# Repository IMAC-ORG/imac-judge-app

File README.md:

# IMAC-Judge-App

# For AeroJudge setup instruction please take a look here
## https://github.com/IMAC-ORG/imac-judge-app/tree/main/scripts

# For developer environment please look below

## Requirements
1. VSCode
2. Docker Desktop
3. Score =>v4.70 with services enabled and started
4. Java 17 or later (Java 21 works fine)

## RUN imac-judge-app
1. Open in a dev container
2. Open new terminal
3. Edit the /var/opt/judge/settings.json file with correct host_ip and port that Score is running on. The file is mounted from the .devcontainer/judge folder and can be modified there instead.
```
sudo vi /var/opt/judge/settings.json

eg.
{
  "judge_id":1,
  "line_number":1,
  "score_host":"192.168.8.100",
  "score_http_port":80,
  "language":"en"
}
```
4. Running the app in the dev container
``` 
cd /workspace
mvn spring-boot:run
```
5. Connecting to the dev container can be done in your local browser http://locahost:8080

## Build imac-judge
1. To build the jar file to be deployed to the PI-SCORE unit.
```
cd judge/
./mvnw clean package
```
Binary {build}.jar located in judge/target folder needs to be copied to the device and extracted in /var/opt/judge/bin
Also {build}-figures.zip file needs to be copied to the device and extracted in /var/opt/judge

## RUN imac-judge-app as a docker container (very similar to running in device)
1. Build imac-judge using above instructions
2. Right-click Dockerfile in root folder and choose Build Image... and name tag imacjudgeapp:latest
3. In terminal run: docker run -p 8080:8080 imacjudgeapp:latest
4. Connecting to the image can be done in your local browser http://locahost:8080

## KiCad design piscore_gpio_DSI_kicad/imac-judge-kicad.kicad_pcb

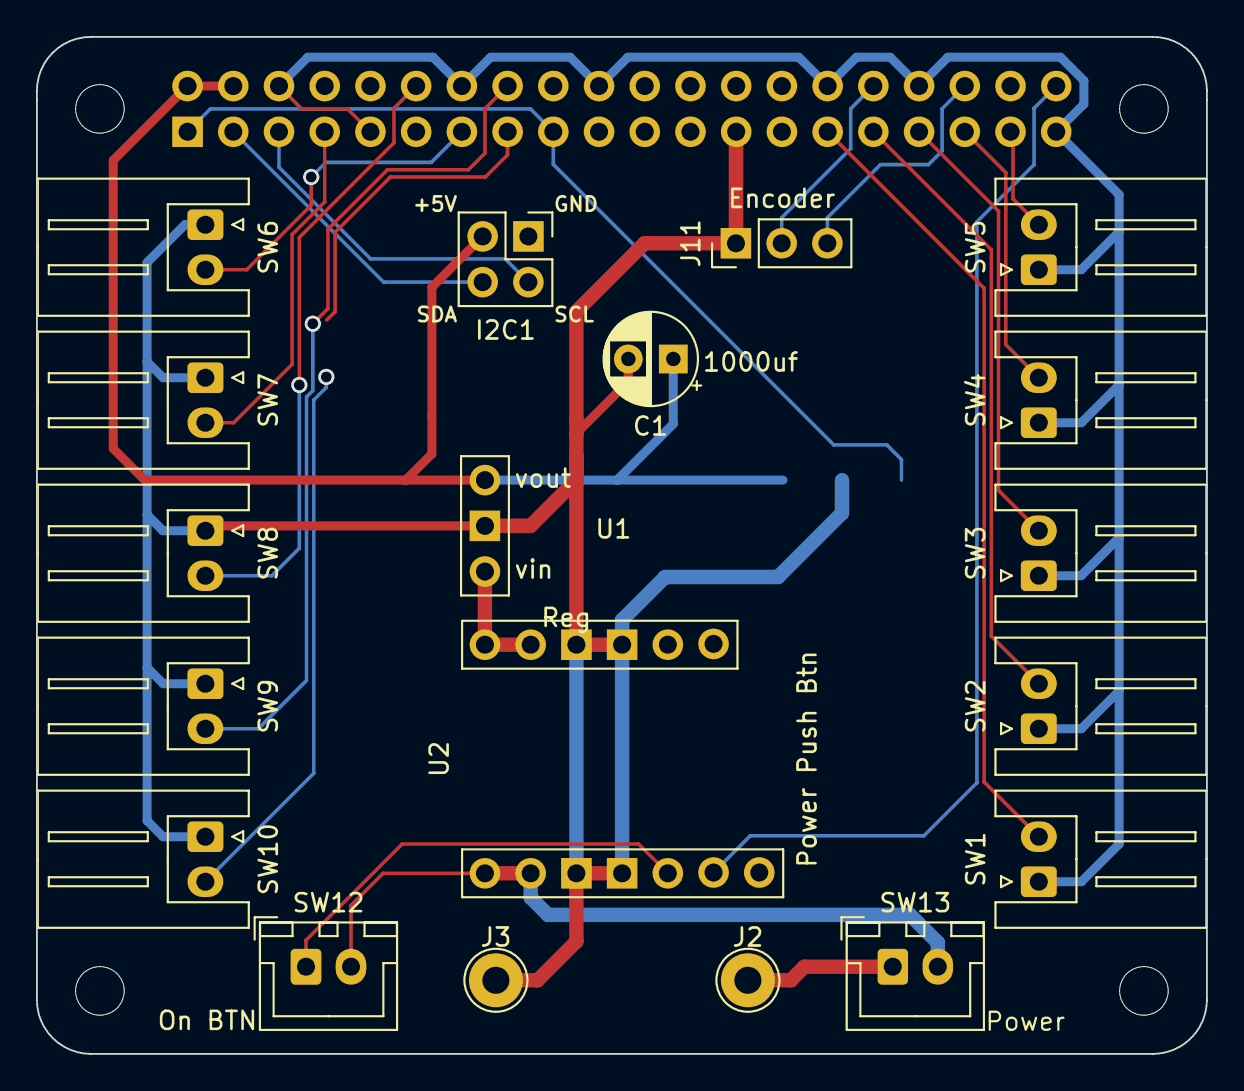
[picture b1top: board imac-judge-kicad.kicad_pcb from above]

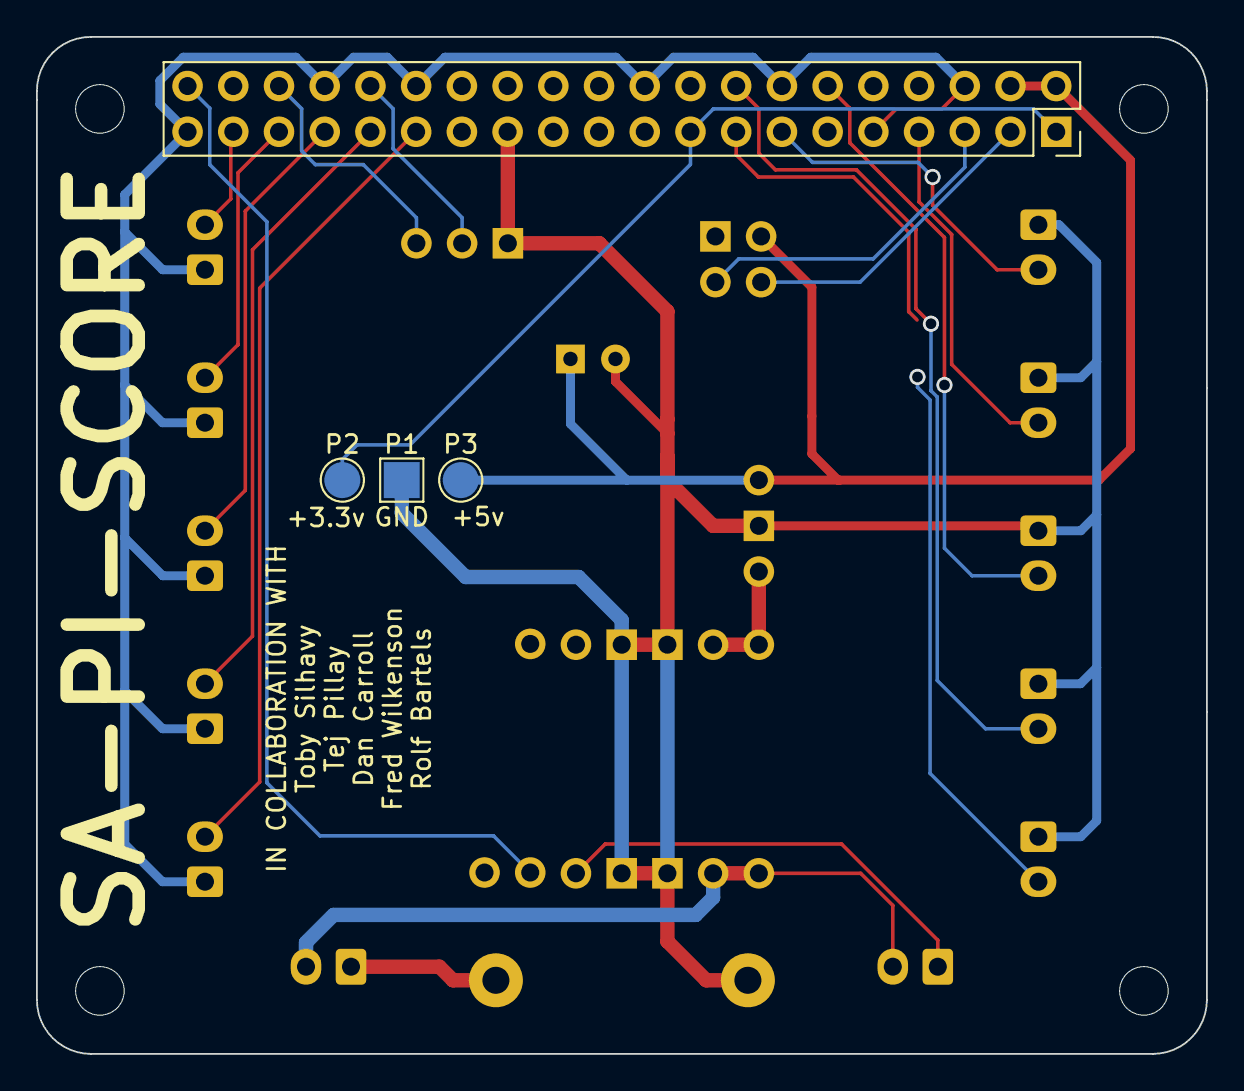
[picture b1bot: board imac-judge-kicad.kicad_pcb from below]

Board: 2 copper layers, 65.0 x 56.5 mm, 27 parts (4 on the bottom side), 22 nets.

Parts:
C1: 1000uf; CP_Radial_D5.0mm_P2.50mm
J1: GPIO; PinSocket_2x20_P2.54mm_Vertical
J2: BATT+; TestPoint_THTPad_D3.0mm_Drill1.5mm
J3: BATT-; TestPoint_THTPad_D3.0mm_Drill1.5mm
J11: Encoder; PinHeader_1x03_P2.54mm_Vertical
MH1, MH2, MH3, MH4: MountingHole_2.7mm_M2.5
P1: GND; TestPoint_Pad_2.0x2.0mm
P2: +3.3v; TestPoint_Pad_D2.0mm
P3: +5v; TestPoint_Pad_D2.0mm
SW1: Button 1; JST_XH_S2B-XH-A_1x02_P2.50mm_Horizontal
SW2: Button 2; JST_XH_S2B-XH-A_1x02_P2.50mm_Horizontal
SW3: Button 3; JST_XH_S2B-XH-A_1x02_P2.50mm_Horizontal
SW4: Button 4; JST_XH_S2B-XH-A_1x02_P2.50mm_Horizontal
SW5: Button 5; JST_XH_S2B-XH-A_1x02_P2.50mm_Horizontal
SW6: Button 6; JST_XH_S2B-XH-A_1x02_P2.50mm_Horizontal
SW7: Button 7; JST_XH_S2B-XH-A_1x02_P2.50mm_Horizontal
SW8: Button 8; JST_XH_S2B-XH-A_1x02_P2.50mm_Horizontal
SW9: Button 9; JST_XH_S2B-XH-A_1x02_P2.50mm_Horizontal
SW10: Button 10; JST_XH_S2B-XH-A_1x02_P2.50mm_Horizontal
SW12: On BTN; JST_XH_B2B-XH-A_1x02_P2.50mm_Vertical
SW13: Power; JST_XH_B2B-XH-A_1x02_P2.50mm_Vertical
U1: Reg; S13V20F5
U2: Power Push Btn; Mini Pushbutton Power Switch
U3: I2C1; PinHeader_2x02_P2.54mm_Vertical

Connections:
+3V3: J1.1, J1.17, P2.1
+5V: C1.1, J1.2, J1.4, P3.1, U1.3 (VOUT), U3.3
+BATT: J2.1, SW13.1 (A)
GND: C1.2, J1.6, J1.9, J1.14, J1.20, J1.25, J1.30, J1.34, J1.39, J3.1, J11.1, P1.1, SW1.1, SW2.1, SW3.1, SW4.1, SW5.1, SW6.1, SW7.1, SW8.1, SW9.1, SW10.1, U1.2 (GND), U2.3 (GND), U2.4 (GND), U3.1
I2C1_SCL: J1.5, U3.2
I2C1_SDA: J1.3, U3.4
Input ENC_A: J1.32, J11.2
Input ENC_B: J1.36, J11.3
Input SW_1: J1.29, SW1.2
Input SW_2: J1.31, SW2.2
Input SW_3: J1.33, SW3.2
Input SW_4: J1.35, SW4.2
Input SW_5: J1.37, SW5.2
Input SW_6: J1.13, SW6.2
Input SW_7: J1.7, SW7.2
Input SW_8: J1.12, SW8.2
Input SW_9: J1.16, SW9.2
Input SW_10: J1.15, SW10.2
MSW: SW12.2, SW13.2 (B), U2.1 (VIN)
PS_BATT+: U1.1 (VIN), U2.2 (VOUT)
PS_OFF: J1.40, U2.7 (OFF)
PS_ON: SW12.1, U2.5 (ON)

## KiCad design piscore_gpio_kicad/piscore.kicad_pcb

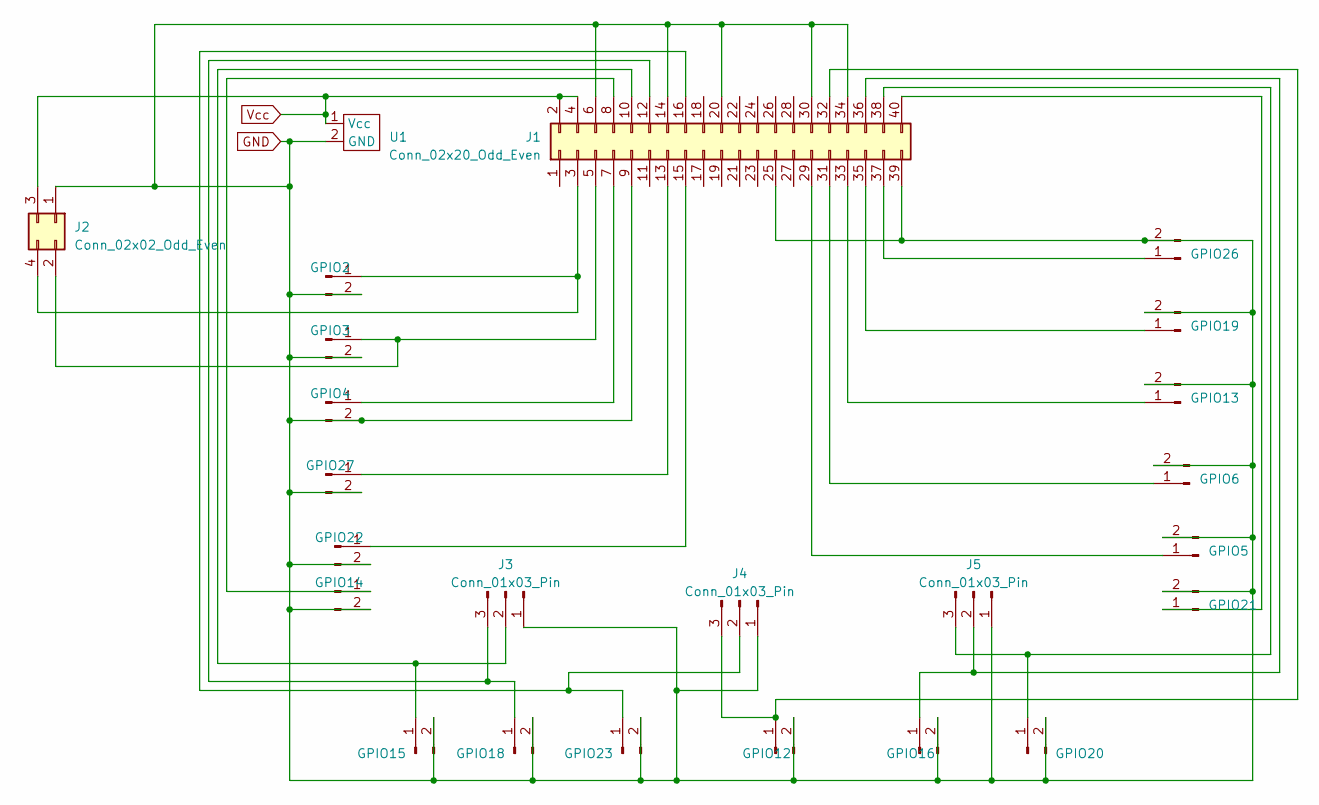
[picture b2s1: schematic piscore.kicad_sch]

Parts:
GPIO2, GPIO3, GPIO4, GPIO5, GPIO6, GPIO12, GPIO13, GPIO14, GPIO15, GPIO16, GPIO18, GPIO19, GPIO20, GPIO21, GPIO22, GPIO23, GPIO26, GPIO27: Conn_01x02_Pin; JST_PH_S2B-PH-K_1x02_P2.00mm_Horizontal
J1: Conn_02x20_Odd_Even; PinHeader_2x20_P2.54mm_Vertical
J2: Conn_02x02_Odd_Even; PinHeader_2x02_P2.54mm_Vertical
J3, J4, J5: Conn_01x03_Pin; PinHeader_1x03_P2.54mm_Vertical
U1: Solder_Pads

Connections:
GND: GPIO2.2, GPIO3.2, GPIO4.2, GPIO5.2, GPIO6.2, GPIO12.2, GPIO13.2, GPIO14.2, GPIO15.2, GPIO16.2, GPIO18.2, GPIO19.2, GPIO20.2, GPIO21.2, GPIO22.2, GPIO23.2, GPIO26.2, GPIO27.2, J1.6, J1.9, J1.14, J1.20, J1.25, J1.30, J1.34, J1.39, J2.1, J3.1, J4.1, J5.1, U1.2 (GND)
unnamed: GPIO2.1, J1.3, J2.4
unnamed: GPIO3.1, J1.5, J2.2
unnamed: GPIO4.1, J1.7
unnamed: GPIO5.1, J1.29
unnamed: GPIO6.1, J1.31
unnamed: GPIO12.1, J1.32, J4.3
unnamed: GPIO13.1, J1.33
unnamed: GPIO14.1, J1.8
unnamed: GPIO15.1, J1.10, J3.2
unnamed: GPIO16.1, J1.36, J5.2
unnamed: GPIO18.1, J1.12, J3.3
unnamed: GPIO19.1, J1.35
unnamed: GPIO20.1, J1.38, J5.3
unnamed: GPIO21.1, J1.40
unnamed: GPIO22.1, J1.15
unnamed: GPIO23.1, J1.16, J4.2
unnamed: GPIO26.1, J1.37
unnamed: GPIO27.1, J1.13
Vcc: J1.2, J1.4, J2.3, U1.1 (Vcc)

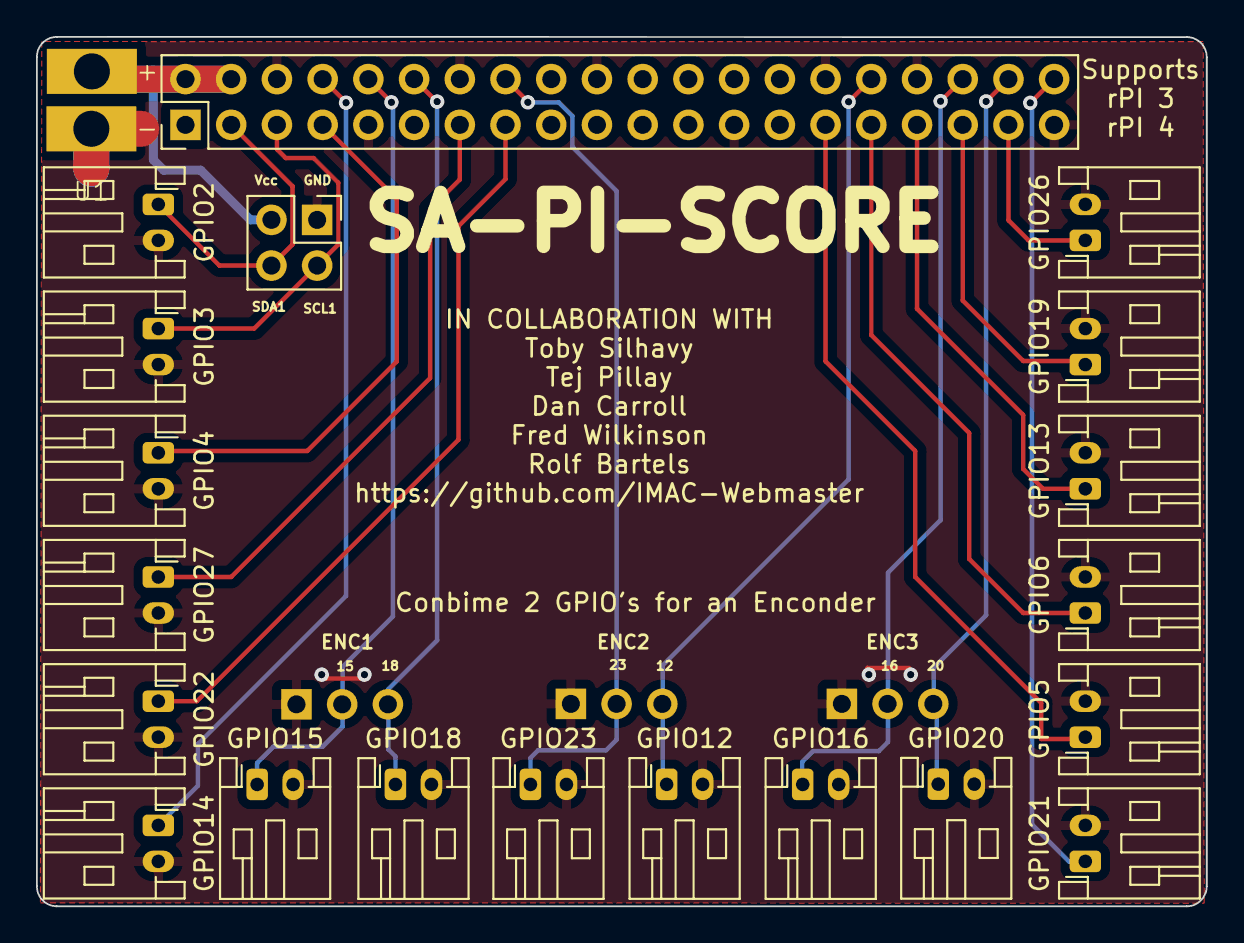
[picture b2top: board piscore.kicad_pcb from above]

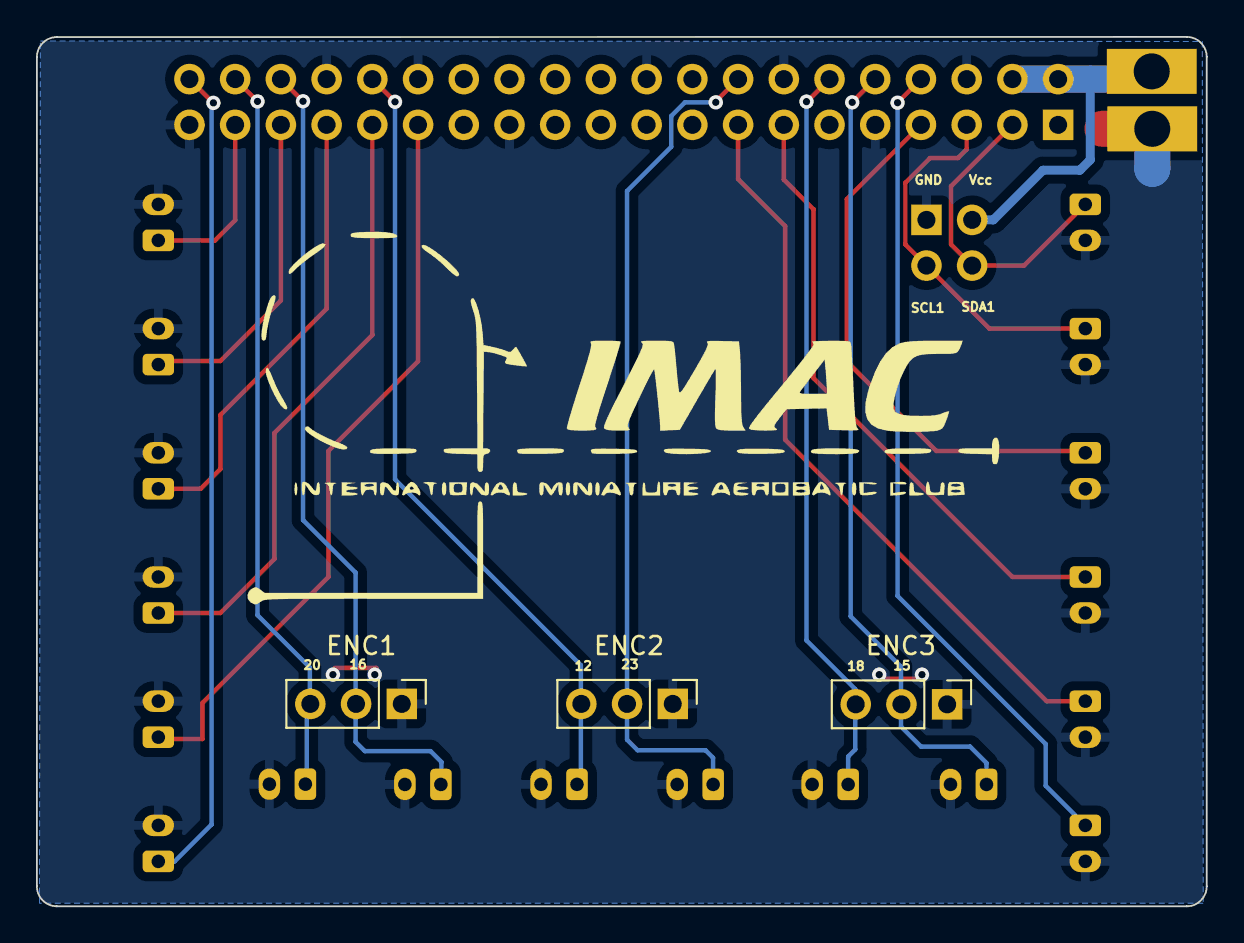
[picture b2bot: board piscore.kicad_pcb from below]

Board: 2 copper layers, 65.0 x 48.3 mm, 24 parts (3 on the bottom side), 20 nets.

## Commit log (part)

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2023-06-28 last update
2023-06-28 final final update
2023-06-30 Audio Update
2023-06-30 Final Audio-Uploads
2023-07-13 Lots of changes. - Code cleanup - rounds (first go) - logging. - changes to comp info - filtered pilot select. - response entity with a hashmap for API returns..
2023-07-13 Fixed score_mode = null bug.
2023-07-14 Updated and image and audio, the name of the svg's and audio files which is mp3 are now reflect the figure # rather than the index.
2023-07-20 Save each score on carousel rotate...
2023-07-21 Review page
2023-07-22 Added David's flip changes from 8adcd68 to pilot-list-round.html
2023-07-24 Removed 'per figure' save... (for now - until service can re-save data).
2023-08-14 Disabling BT
2023-08-15 Setup Update
2023-08-15 syntax correction
2023-08-16 Updated Fig 8C for Unlimited
2023-08-16 sdssd
2023-08-19 added pilots
2023-08-21 addeed
2024-01-03 2024 Sequence
2024-01-27 fixed up code
2024-01-28 Changed judge_update.sh to fetch latest release if available
2024-01-29 Removing separate alt figures zip
2024-02-04 Added ability to switch between std and alt sequences, line # header
2024-02-07 Change to github action to use latest docker image
2024-03-20 Fixed figures displaying for unknowns
2024-03-30 updates for 3.5in screens
2024-04-02 Cleaned errant entry
2024-04-04 logging level fix
2024-04-06 Fix code to convert Windows config path to unix style for figures
2024-04-06 Class Select Page
2024-04-07 Change Class Select to a modal instead,
2024-04-15 Button sizing corrected for diffrent screen sizes
2024-07-04 Update build actions to v4 as v3 is depricated
2024-09-29 Added volume service for a rotary encoder using ENC1
2024-10-12 Changed figure name/description to have unknowns treated same as known and basic class (always includes description from Score)
2025-04-26 Added APIs to manage settings
2025-04-27 Updated score sync errors to stay on screen longer and show error properly for failures to sync scores
2025-05-26 Updated setup and update scripts
2025-08-11 Fix filters to preserve on Home and update judge select dialog
2025-08-18 Changed IMAC # to be String to match Score entry
2025-09-13 Updated Create Tag workflow to be more dynamic
2025-09-28 Added score timeout settings, Added countdown timer to next info status update
2025-11-23 Remove CI/CD workflows for isolated development
2025-11-24 Add project documentation (dpg_docs)
    Include figures restructure project guide and related documentation.
2025-11-24 Improve battery indicator to only show warnings
    - Hide indicator when battery is OK (40%+)
    - Show warning style at 20-40% (orange)
    - Show critical alert below 20% (red)
    - Check battery on modal open instead of page load
    - Always fetch fresh data (no caching)
2025-11-24 UI refinements for pilot selection and judging pages
    - Refined pilot list cards: removed icons, increased text sizes, pastel yellow background
    - Reduced pilot_class font size for better spacing (5.5vw + 2.5vh)
    - Enlarged pilot name on judge selection modal (2.5rem)
    - Fixed judging page round/seq/dir display based on type:
    * KNOWN: shows Round, Seq, Dir
    * UNKNOWN: shows Round, Dir (no Seq)
2025-11-25 Add admin pages and freestyle figure display improvements
    - Create adminComp.html for scorekeeper administration (event data, round settings)
    - Create adminDevice.html for device settings (scoring mode)
    - Create adminScores.html placeholder for future score management
    - Add routes for /admin/comp, /admin/device, /admin/scores
    - Hide "Figure X" prefix for FREESTYLE rounds on judging screen
    - Update v2.0 documentation with spelling fixes and structure improvements
2025-11-26 Code cleanup: fix deprecated APIs and comment unused imports
    - Comment out unused imports with REVIEWED-UNUSED tag
    - Update deprecated new URL(x) to URI.create(x).toURL()
    - Update deprecated Runtime.exec() to ProcessBuilder
    - Comment out unused fields and TODO comments
2025-11-26 Update TODO.md with new priorities and preserve legacy items for review
2025-11-27 Disable judge buttons for unavailable sequence types and improve fallback UX
    - Add getClassesWithUnknown() and hasFreestyle() to ScheduleService to check
    sequences.dat for available round types
    - Grey out UNKNOWN/FREESTYLE buttons in judge modal when no sequences exist
    - Improve noseq.html fallback page with warning and return button
    - Rename sequence_validation_error.html to sequence_validation.html
    - Widen success button on validation page for better UX
2025-11-27 Add git workflow docs and event folder, update vscode settings
2025-11-28 Add score mismatch resolution feature and deadline button TODO
    - Add mismatch detection API and resolution UI for fixing wrong pilot scores
    - Add adminScoresResolve.html template for resolution workflow
    - Update adminScores.html with resolve mismatches button
    - Add documentation for score mismatch resolution feature
    - Add TODO for deadline button feature (-3 score conversion)
2025-12-09 Move v2.0 release notes to docs/, remove personal working files
    - Move release notes to docs/v2.0-Release-Notes.md for shared access
    - Remove dpg_docs/ from tracking (personal working notes)
    - Add dpg_docs/ to .gitignore
2025-12-09 Remove unused gitignore entries
2025-12-14 Remove all REVIEWED-UNUSED commented imports and fields
    Delete 28 commented items across 11 files that were previously
    tagged as unused in 2025-11. All verified as truly unused:
    - Logger/LoggerFactory in SettingUtils
    - JudgeApplication, Properties in CommandLineAppStartupRunner
    - ZipEntry in SettingService
    - URL, ResourceUtils, Gson in SequenceService
2026-01-10 Adjusted pilot service to allow filtering inactive pilots from the carousel's and other needed areas
2026-01-10 Fixed admin pages to use proper setting values, adjusted headers to not overwrite banner, fixed updateSettings to work with Windows when developing
2026-01-10 Refactored getBattery methods to reduce code duplication
2026-01-10 Updated methods to support docker build to move away from older copy plugin which stopped working
2026-01-10 Increase text size of warning message
2026-01-11 Refactor sequence_validation handling to consolidate errors and warnings into a simplified structure, enhancing clarity and maintainability. Update related classes and HTML template for improved disp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
2026-01-11 Fixed issue with language setting in path for error with image
2026-01-11 Changed to use sh in settingservice to support both device and docker
2026-01-11 Added method to retrieve unknown figures zip from Score during new event load and re-sync process
2026-03-13 Added a couple of useful scripts
2026-03-14 Enhance direction toggle functionality #108
2026-03-14 Corrected settings format
2026-04-01 Updated version number
2026-04-01 Removed side-load option - another option will be added later
2026-04-02 Increase time to show success message for restart
2026-04-02 Changed retries down to 30
2026-04-26 Change default score host and port to match the current AeroJudge standard
2026-04-27 Workflow changes (tag/build only when changing program and not scripts/docs/etc.)
2026-04-27 Updated build to only allow one pre-release (new ones remove the last one)
2026-05-03 fix(move-round): activeRound integrity
    moveRound was force-writing both pilots' activeRound to destRound + 1.
    Wrong for any non-equal-count case — source's stored activeRound ended up
    disconnected from its actual count, bricking the next score-entry attempt
    on that pilot until activeRound was corrected.
    Replace with explicit decrement (source) + increment (destination) matching
    the actual delta of the move. Adds decrementActiveRound on PilotScores
2026-05-03 feat(scores): extract pure-logic helpers to ScoreResolverService
    New @Service mirroring SequenceValidationService — no own state, autowires
    PilotService. Houses the resolver's pure-logic helpers so the controller
    stays a thin HTTP layer.
    Moved verbatim from APIController:
    - getMismatches() — body of /api/scores/mismatches
    - countRoundsForType(...) — utility used by every resolver eligibility
2026-05-03 feat(scores/move-round): eligibility checks
    moveRound previously accepted any (sourcePilotId, destPilotId, roundType,
    sourceRound) and applied the move blindly. Adds three backend rejections
    matching the wizard's pre-flight rules so the API enforces eligibility
    itself:
    - Source has no extra round to give (sourceCount <= destCount).
    - Source has an unresolved missing seq 2 — Fix Missing Sequence first on
2026-05-03 feat(admin/menu): new /admin landing page
    Three full-width tiles (Event Admin, Score Fixes, Device Settings) linking
    to the existing admin pages. Whole tile is the link; no icons on tile
    titles. Header carries only an Exit button — this page is the menu, so a
    FAB nav menu inside it would be redundant.
    Tile descriptions are friendly UX text rather than the spec's mechanical
    parenthetical lists:
2026-05-03 feat(admin/event-name): event name on landing + validation page
    Displays the loaded comp's event name prominently on the two highest-traffic
    admin entry points so admins recognize what's loaded before acting on it.
    Closes the test/live event confusion gap.
    - /admin landing: single text line between the page header and the first
    tile, just the event name (no "Event:" prefix).
    - sequence_validation.html: centered subtitle row under the page heading,
2026-05-03 feat(scores/swap-round-ui): tile + wizard
    Adds the Swap Round Scores tile on /admin/scores (between Resolve
    Mismatches and Zero Unflown Rounds; swap_horiz icon, blue-text) and the
    swap wizard at /admin/scores/swap.
    Wizard flow: class/type picker (filtered to groups with >= 2 pilots that
    share a common round; per-class rows for Known/Unknown, FREESTYLE on its
    own row) -> round picker (only rounds where >= 2 pilots have a PScore)
2026-05-03 chore(ui): admin DESIGN.md tier sweep
    Applies DESIGN.md text-size and spacing tiers to all admin templates:
    Text tiers (1.5 / 1.75 / 1.9 / 2.1 rem):
    - Small (1.5rem): captions, meta labels, hint text, warning notes,
    modal secondary text, inline icons.
    - Body (1.75rem): labels, list rows, paragraphs, modal primary text,
    wizard button labels, wizard context strip.
2026-05-03 docs(changelog): admin pages overhaul
    New CHANGELOG entry covering the full 21-commit overhaul: detection
    rewrite, ScoreResolverService, the four resolver operations (Fix
    Missing Sequence, Move Round, Zero-fill, Swap Round Scores), the
    format-change preventive blocker, the admin landing page and nav
    restructure, the event-name display, the wizard UIs, the pre-sync
    mismatch modal, the DESIGN.md tier sweep, the Score Fixes tile layout
